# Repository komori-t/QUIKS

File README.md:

# QUIKS

QUIKS unifies inexpensive kinetic sensors

## About

QUIKS is an inexpensive motion tracking system.

It is consists of one terminal node and multiple sensor nodes.

Each node has a sensor and the terminal node bridges PC and them.

## QUIKS is ...

### 1. Inexpensive

QUIKS is designed to construct motion tracking system at low cost.

### 2. Extendable

New node can be added by just connecting to RS485 bus.

It is easy to develop new kind of node to extend the system.

### 3. Scalable

More nodes you connect, more data you get.

So you can omit any nodes to reduce costs, areas, times, etc.

If you do not need to track the lower half of your body, you can only upper half nodes for example.

## Currently available node

### IMUTracker

The IMUTracker is a kind of node that captures rotation of one bone.

It has IMU sensor ICM20948 controlled by a tiny microcontroller LPC802.

### USB terminal node

USB terminal node is a kind of terminal node that communicates with PC through USB.

It acts as virtual serial port and bridges USB and RS485 bus.

IMUTracker and USB terminal node shares the same design of circuit to reduce manufacturing costs.

## Other nodes to be added (hopefully)

### Wireless terminal node

Wireless terminal node is a kind of teminal node that communicates with PC wirelessly (maybe in 900 MHz band).

### Absolute position tracking node

If the position of one bone (typically waist) can be detected, it is possible to move around in virtual world.

## Documentation

A technical memo (in the form of paper) of IMUTracker can be found [here](https://gist.github.com/komori-t/2a9c5ed3c2d6123b80474edbda02dfcf/raw/6774a583ee427da89996ef7d9e91693c2fbc6523/imutracker.pdf).

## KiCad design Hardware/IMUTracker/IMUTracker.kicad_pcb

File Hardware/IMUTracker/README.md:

# IMUTracker

## Design and connectivity
IMUTracker system is consisted of two different designs, Base and Single. Both uses same IMUTracker sensor on it, also Base uses MicroUSB to RS485 convertor as well. The Base have micro usb port, and entire QUIKS will be connected to PC through this port.

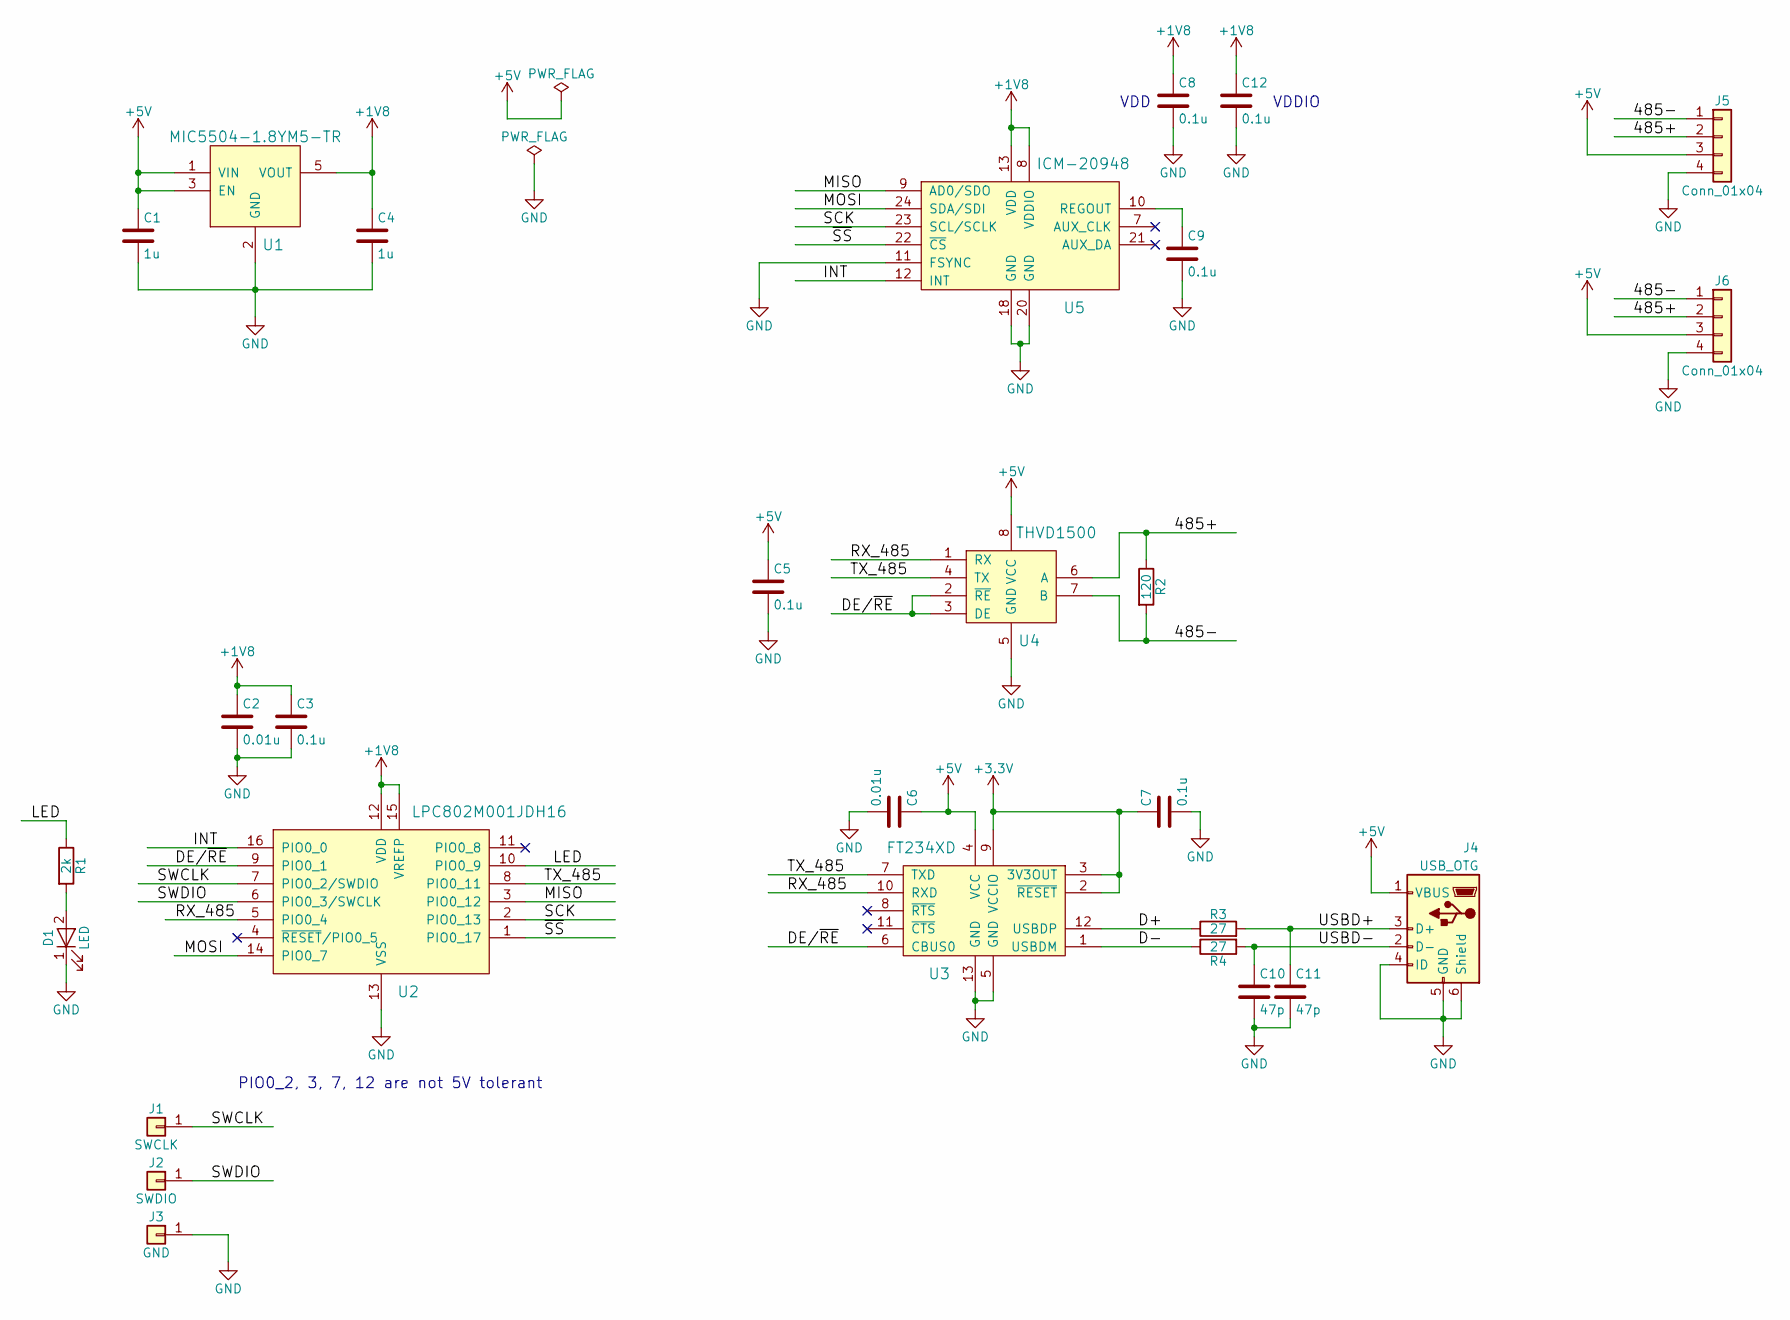
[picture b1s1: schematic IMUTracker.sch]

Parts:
C1, C4: 1u; C_0603
C2, C6: 0.01u; C_0603
C3, C5, C7, C8, C9, C12: 0.1u; C_0603
C10, C11: 47p; C_0603
D1: LED; LED_0603
J1: SWCLK; Measurement_Point_Round-SMD-Pad_Small
J2: SWDIO; Measurement_Point_Round-SMD-Pad_Small
J3: GND; Measurement_Point_Round-SMD-Pad_Small
J4: USB_OTG; ZX62-B-5PA
J5, J6: Conn_01x04; JST_PA_04_Angled
R1: 2k; R_0603
R2: 120; R_0603
R3, R4: 27; R_0603
U1: MIC5504-1.8YM5-TR; SOT-23-5
U2: LPC802M001JDH16; TSSOP-16_4.4x5mm_Pitch0.65mm
U3: FT234XD; DFN-12-1EP_3x3mm_Pitch0.45mm
U4: THVD1500; SOIC-8_3.9x4.9mm_Pitch1.27mm
U5: ICM-20948; ICM20948

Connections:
+1V8: C2.1, C3.1, C4.1, C8.1, C12.1, U1.5 (VOUT), U2.12 (VDD), U2.15 (VREFP), U5.8 (VDDIO), U5.13 (VDD)
+3V3: C7.1, U3.2 (~RESET), U3.3 (3V3OUT), U3.9 (VCCIO)
+5V: C1.1, C5.1, C6.1, J4.1 (VBUS), J5.3, J6.3, U1.1 (VIN), U1.3 (EN), U3.4 (VCC), U4.8 (VCC)
/485+: J5.2, J6.2, R2.1, U4.6 (A)
/485-: J5.1, J6.1, R2.2, U4.7 (B)
/D+: R3.1, U3.12 (USBDP)
/D-: R4.1, U3.1 (USBDM)
/DE/~RE: U2.9 (PIO0_1), U3.6 (CBUS0), U4.2 (~RE), U4.3 (DE)
/INT: U2.16 (PIO0_0), U5.12 (INT)
/LED: R1.1, U2.10 (PIO0_9)
/MISO: U2.3 (PIO0_12), U5.9 (AD0/SDO)
/MOSI: U2.14 (PIO0_7), U5.24 (SDA/SDI)
/RX_485: U2.5 (PIO0_4), U3.10 (RXD), U4.1 (RX)
/SCK: U2.2 (PIO0_13), U5.23 (SCL/SCLK)
/SWCLK: J1.1, U2.7 (PIO0_2/SWDIO)
/SWDIO: J2.1, U2.6 (PIO0_3/SWCLK)
/TX_485: U2.8 (PIO0_11), U3.7 (TXD), U4.4 (TX)
/USBD+: C11.1, J4.3 (D+), R3.2
/USBD-: C10.1, J4.2 (D-), R4.2
/~SS: U2.1 (PIO0_17), U5.22 (~CS)
GND: C1.2, C2.2, C3.2, C4.2, C5.2, C6.2, C7.2, C8.2, C9.2, C10.2, C11.2, C12.2, D1.1 (K), J3.1, J4.4 (ID), J4.5 (GND), J4.6 (Shield), J5.4, J6.4, U1.2 (GND), U2.13 (VSS), U3.5 (GND), U3.13 (GND), U4.5 (GND), U5.11 (FSYNC), U5.18 (GND), U5.20 (GND)
unnamed: C9.1, U5.10 (REGOUT)
unnamed: D1.2 (A), R1.2

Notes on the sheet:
VDDIO
VDD
PIO0_2, 3, 7, 12 are not 5V tolerant

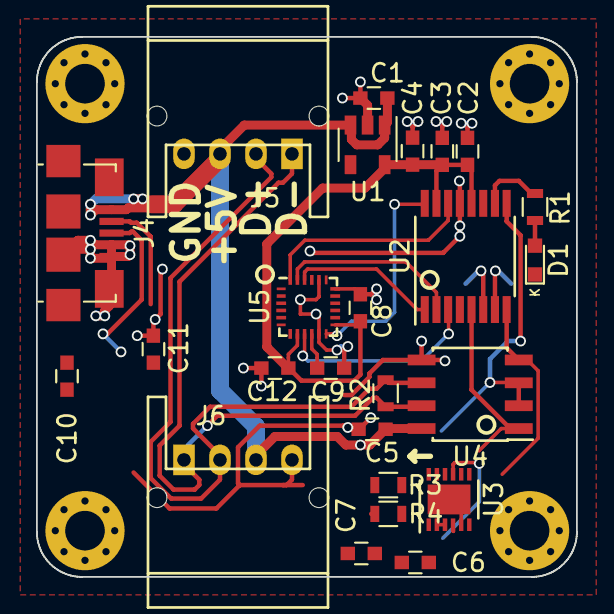
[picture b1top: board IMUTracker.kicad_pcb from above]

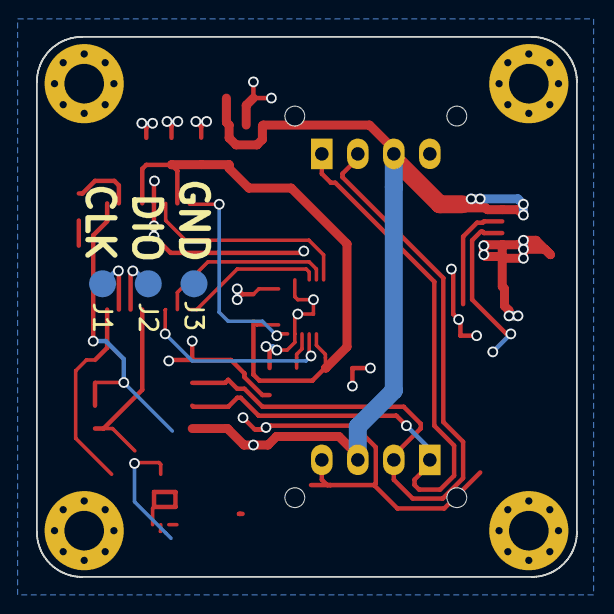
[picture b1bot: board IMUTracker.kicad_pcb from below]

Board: 2 copper layers, 30.0 x 30.0 mm, 28 parts (3 on the bottom side), 23 nets.

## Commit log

2019-11-17 Add IMUCapture board step cad model, add prototye-version casing CAD model (this will be replaced to new later)
2019-11-17 Rename IMUCapture.step --> IMUTracker.step
2019-11-17 add binary attributes
2019-11-17 Update .gitignore as a preparation of adding autodesk inventor's file
2019-11-17 Rename Housing.SLDPRT --> IMUTracker_casing_v1.SLDPRT, add full assemble of QUIKS
2019-11-17 change location of image
2019-11-17 Add appearance image
2019-11-17 Move image to bottom side
2019-11-17 add STL file for 3d printing, accordingly add & change directoriy
2019-11-18 Changed directory structure, remove appearance image
2019-11-18 Update IMUTracker_assemble.iam according to the change of directory structure, add README into Hardware/IMUTracker, uplpad step cad model of full assemble.
2019-11-18 Update .gitattributes
    ipt & iam are Inventor's file format. stl is 3d print data format, and step is a exchange format.
2019-11-18 Fix image url in gist
2019-11-19 Specified IMUTracker/Casing/ directory as binary. Update step cad file (maybe automatic backup save with clising this file last time)
2019-11-19 Fix typo (?) QUICKS --> QUIKS on top README
2019-11-19 Fixed wildcard usage on .gitattributes
2019-11-19 add LF at the end of top README
2019-11-19 Add PCB design and CNC program.
2019-11-19 Draw 3D model on Inventor, attached PA-4 cad model imported from JST website
2019-11-19 WIP IMUTrackerBase
2019-11-19 Designed 8-port hub board, add cnc milling data
2019-11-21 Modify IMUTrackerBase and base ASM, attach micro usb connector holder. Also add STL and STEP exchange format.
2019-11-21 Create separated dicectory onto Hardware/IMUTracker/Casing/ and add new design of Base
2019-11-21 Change directory stracture on Hardware/IMUTracker/Casing
2019-11-21 Erase duplicated files on previous commit
2019-11-21 add LF on EOF
2020-01-01 Convert IMUTracker pcb 3d model from STEP to Inventor ipt/iam file, and group them onto IMUTracker_Inventor_model folder
2020-01-01 Update assemble files regarding changes of IMUTracker PCB CAD model
2020-01-01 Add new sub-workspace directory
2020-01-01 Add IMUTrackerBase as a directory reserved for binary files.
2020-01-01 Convert IMUTracker.step to Inventor CAD model and group them onto a new folder
2020-01-01 Update Inventor project file
2020-01-07 inline functions to improve performance
2020-01-07 add license agreement
2020-01-08 implement boot loader
2020-01-08 update page usage check
2020-01-08 add rescue program
2020-01-08 implement fast clz
2020-04-30 add IMUTracker paper
2020-05-22 complete IMUTracker paper
2020-05-22 add documentation to README
2021-12-28 add complete demo program
